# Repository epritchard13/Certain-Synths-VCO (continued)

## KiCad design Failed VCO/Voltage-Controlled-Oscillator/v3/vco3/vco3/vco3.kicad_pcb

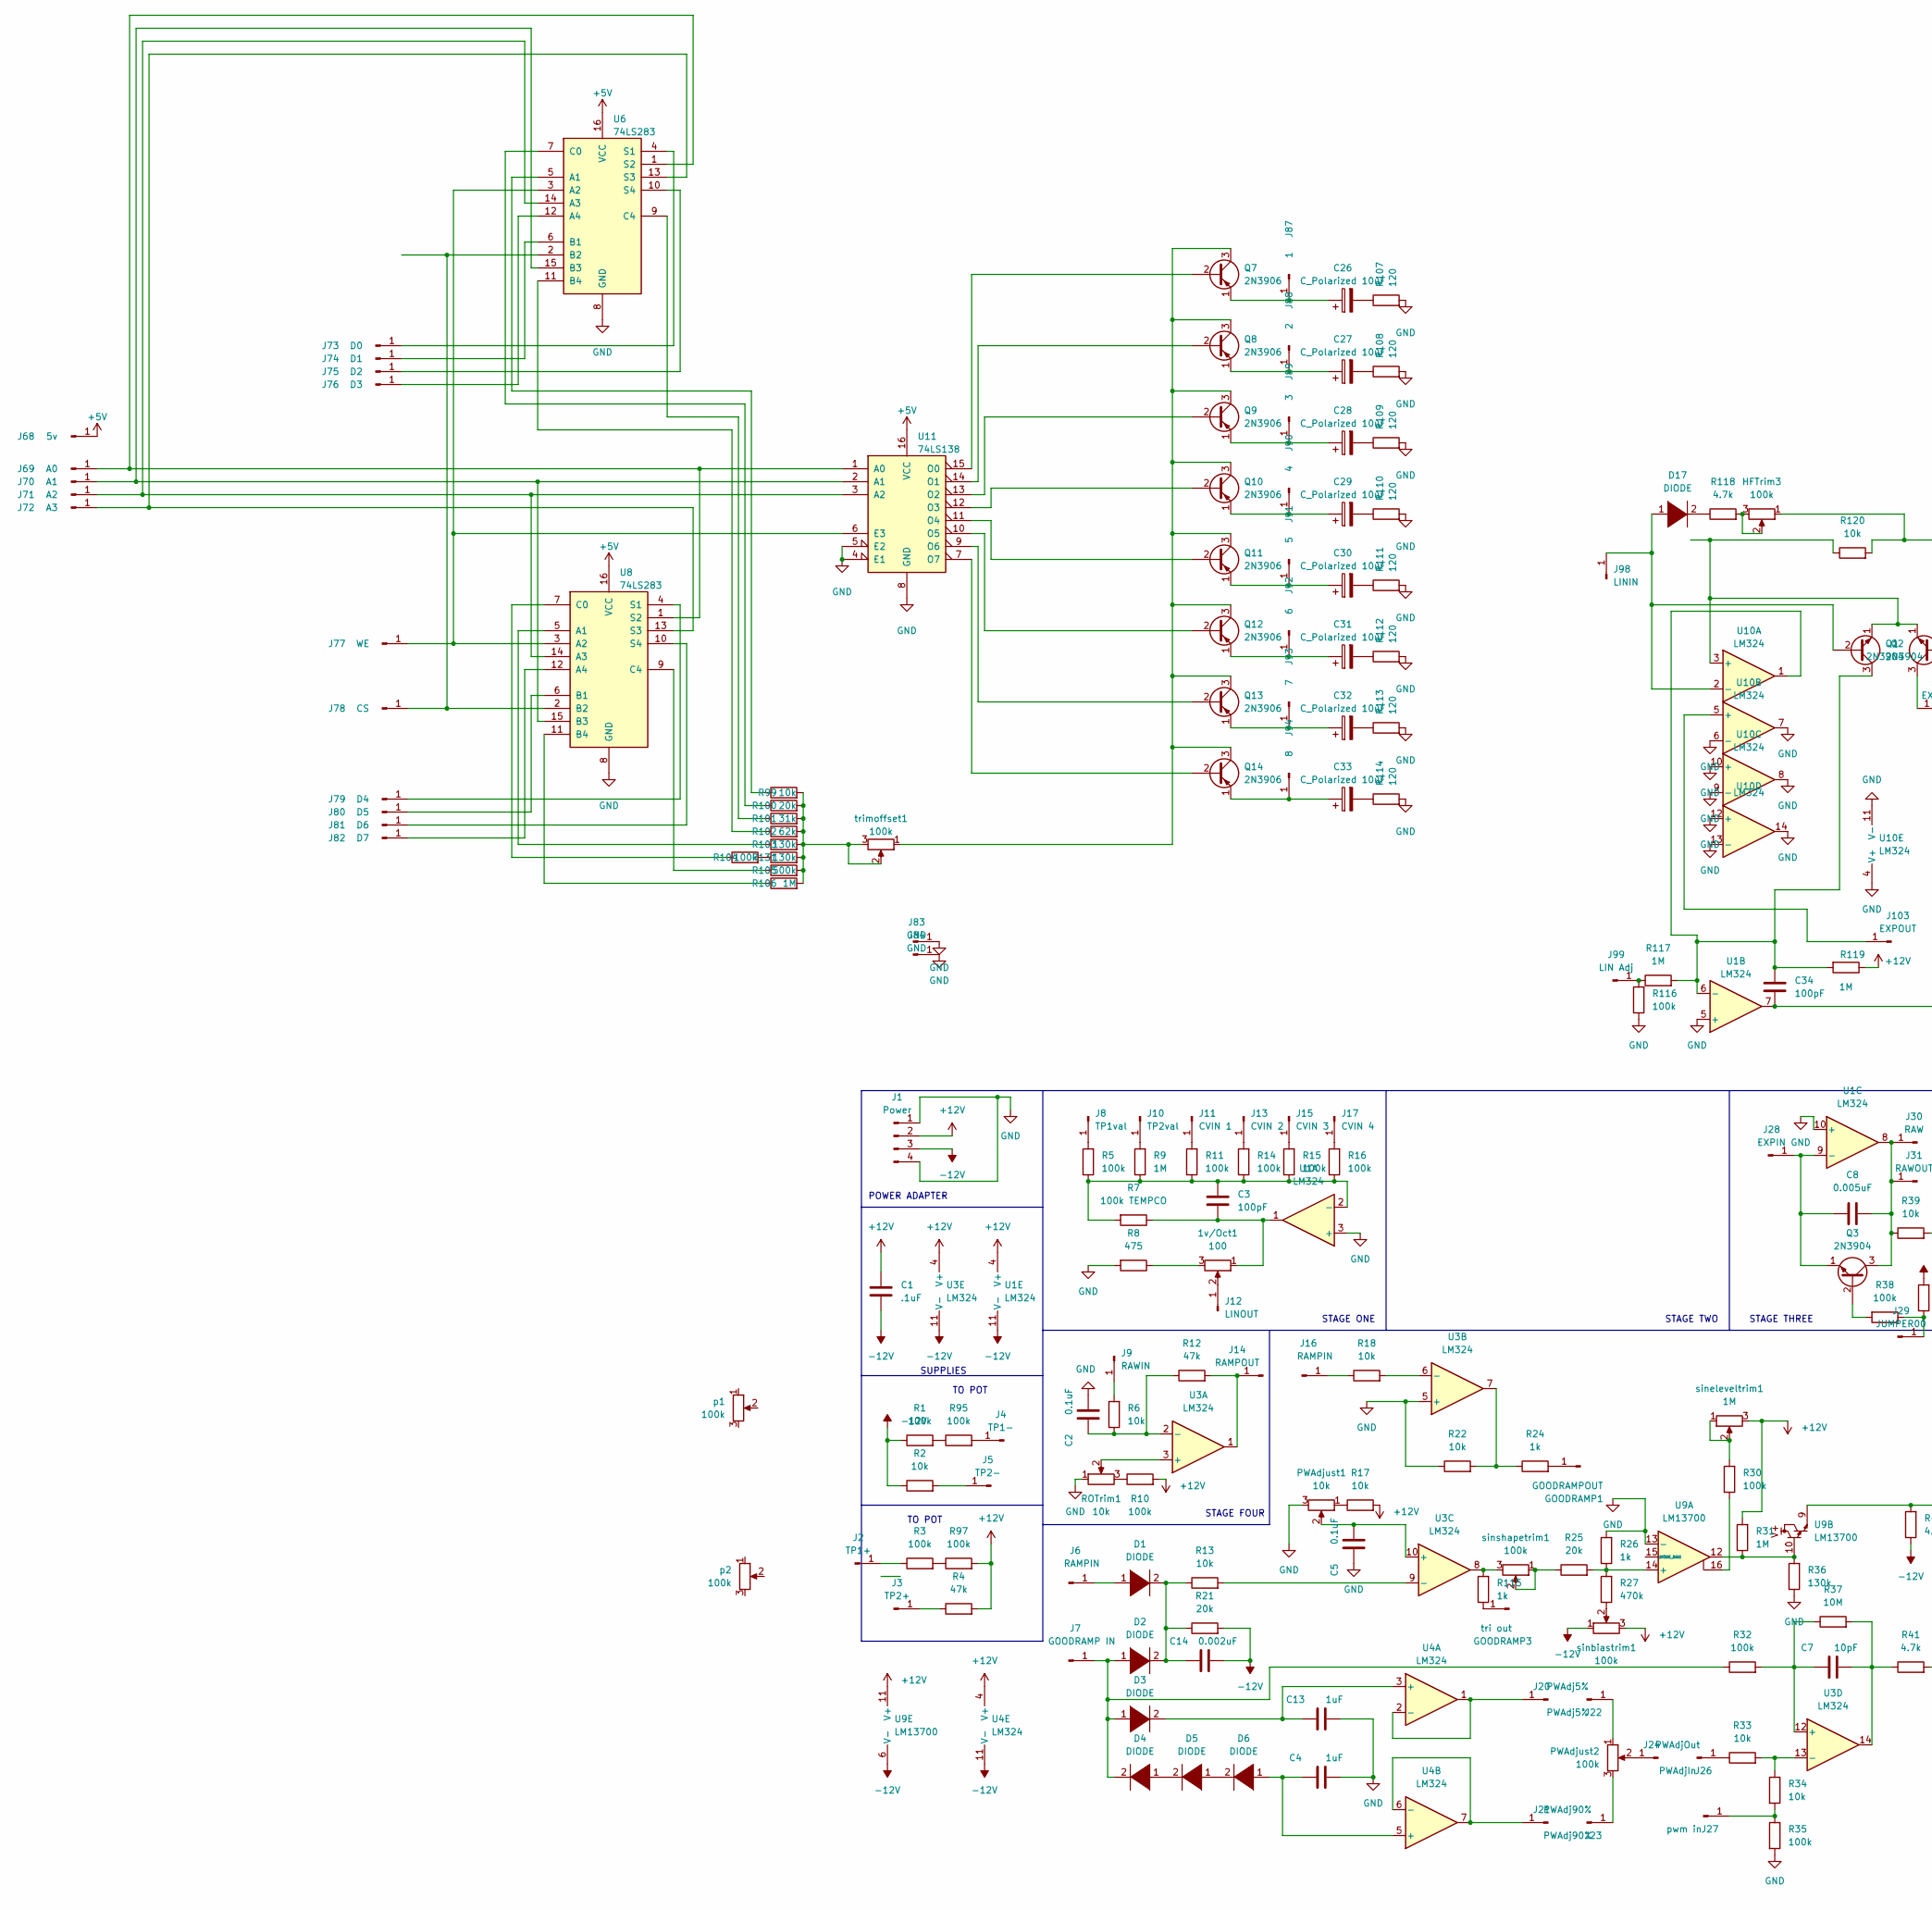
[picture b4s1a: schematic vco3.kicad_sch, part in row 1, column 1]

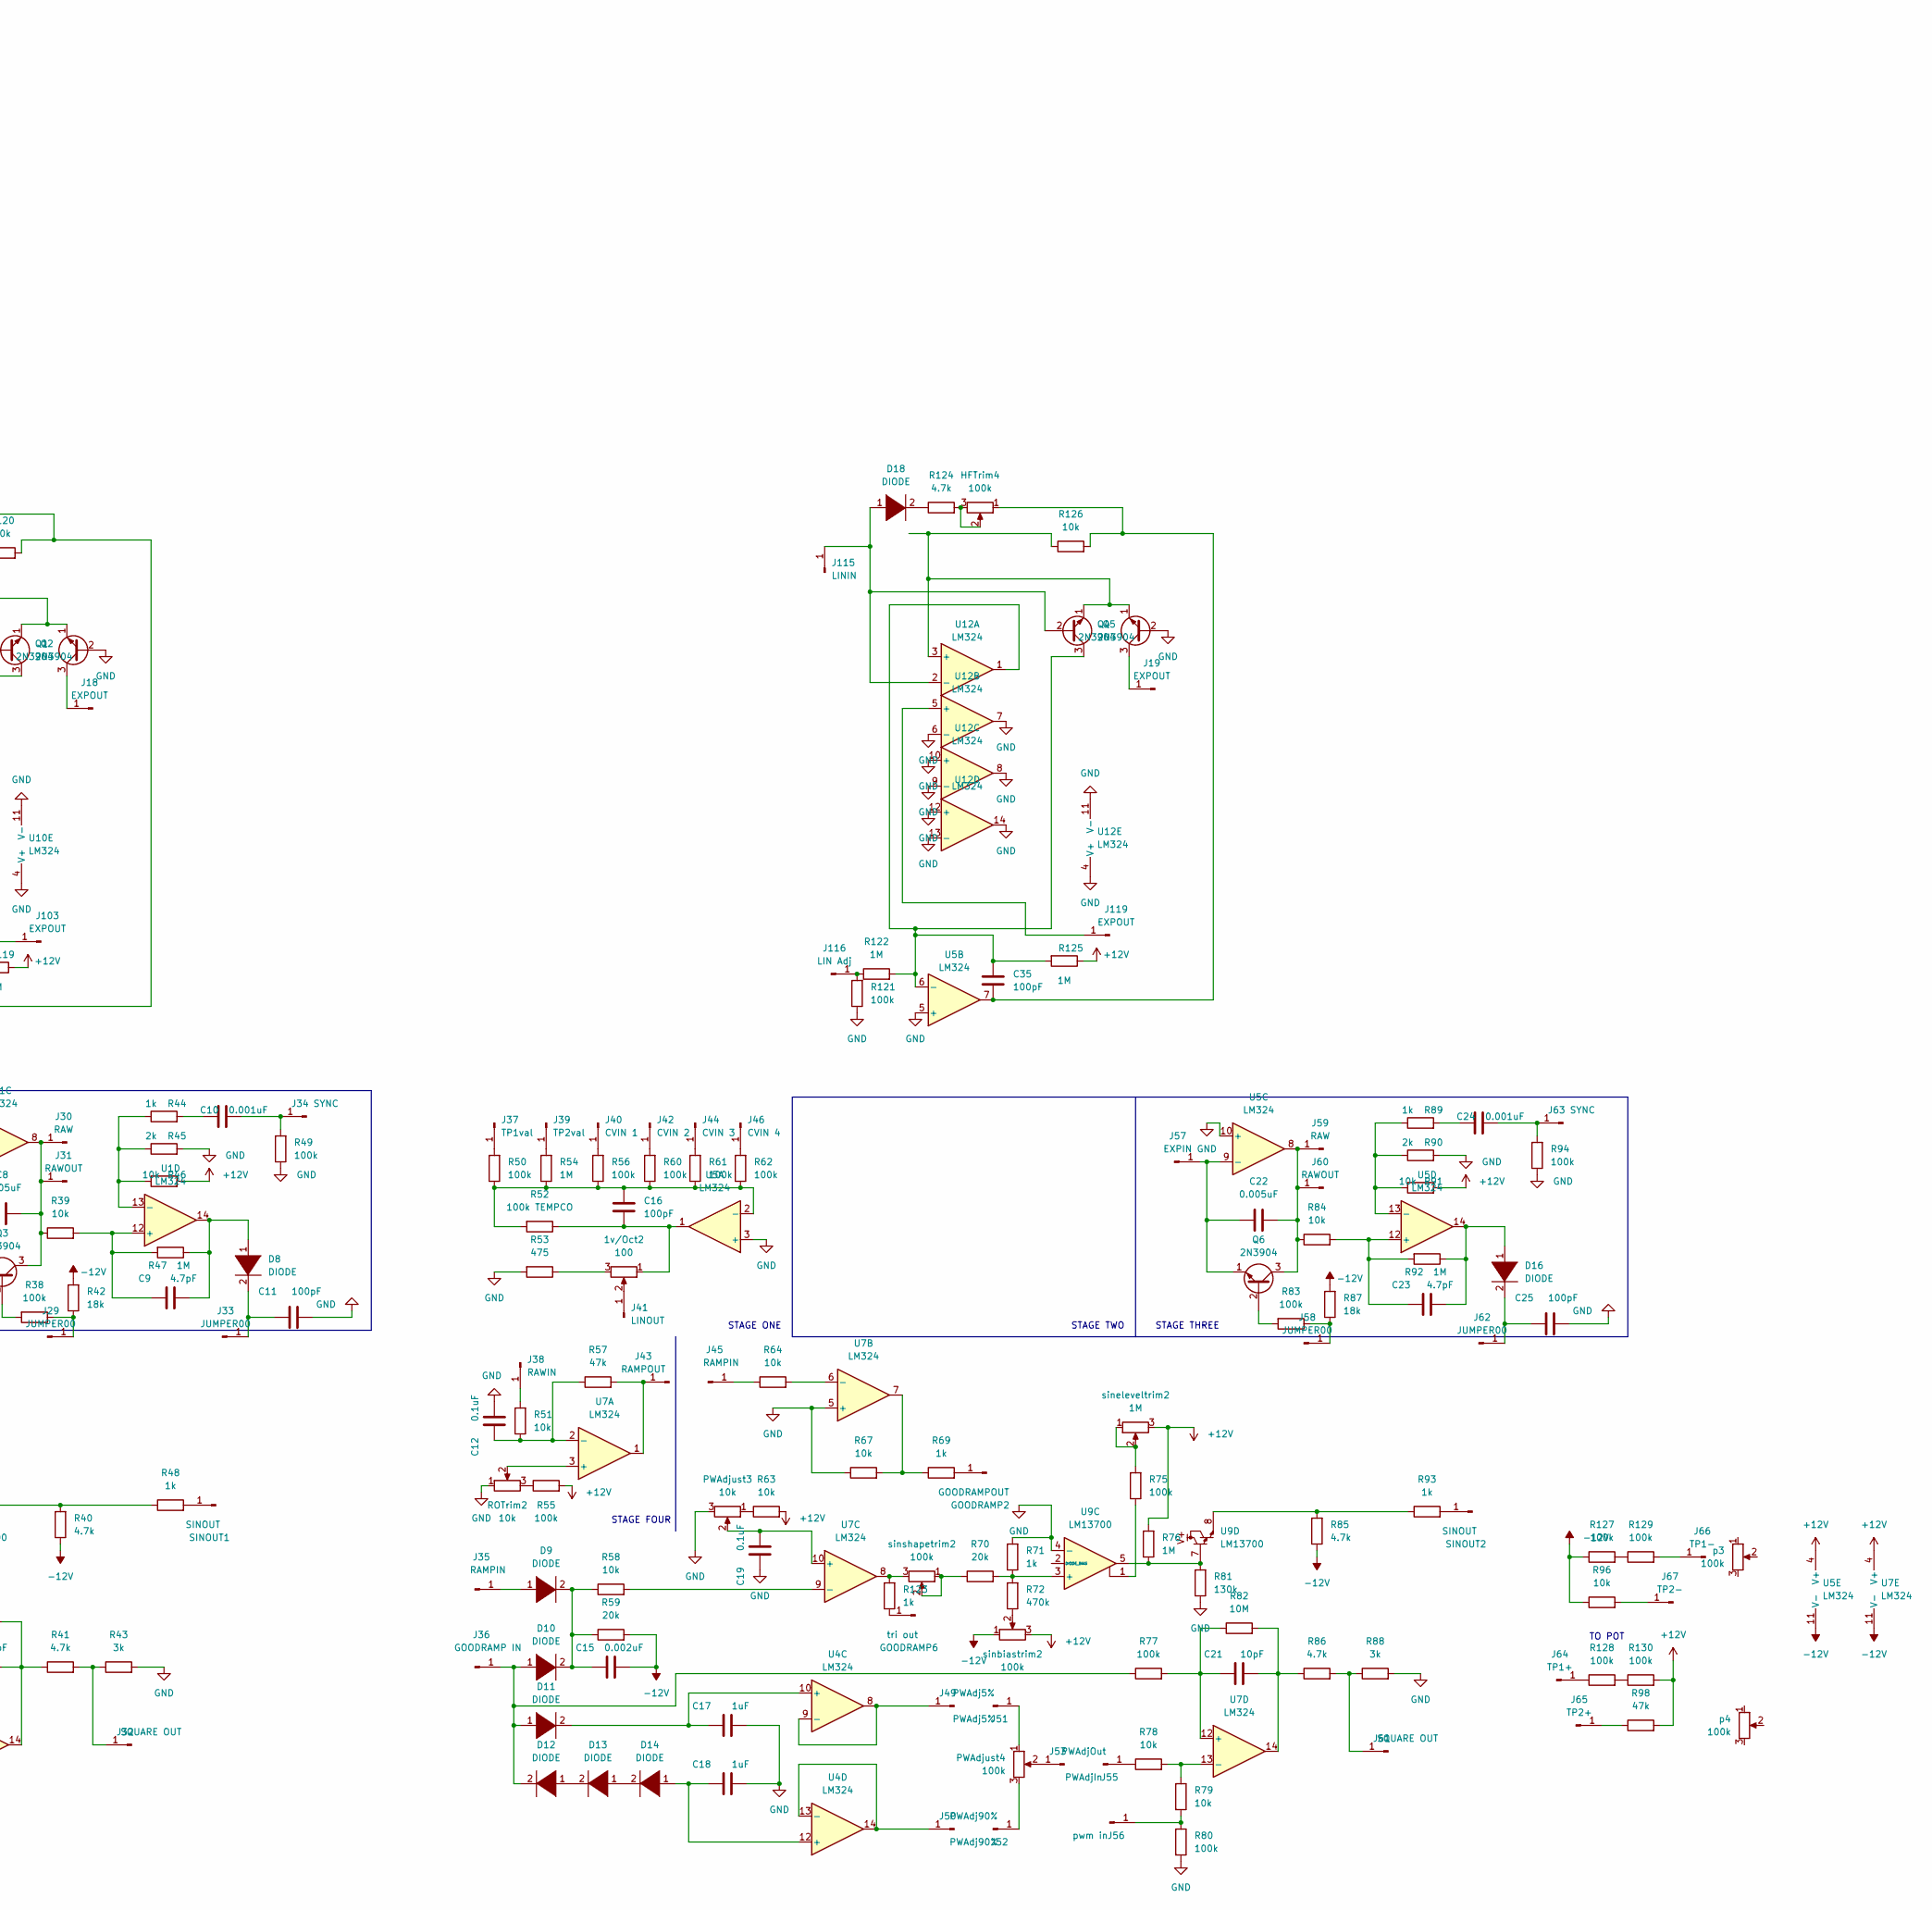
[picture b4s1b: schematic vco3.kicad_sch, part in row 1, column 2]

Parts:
1v/Oct1, 1v/Oct2: 100; Potentiometer_ACP_CA6-H2,5_Horizontal
C1: .1uF; C_Disc_D3.0mm_W2.0mm_P2.50mm
C2, C5, C12, C19: 0.1uF; C_Disc_D3.0mm_W2.0mm_P2.50mm
C3, C11, C16, C25, C34, C35: 100pF; C_Disc_D3.0mm_W2.0mm_P2.50mm
C4, C13, C17, C18: 1uF; C_Disc_D3.0mm_W2.0mm_P2.50mm
C7, C21: 10pF; C_1206_3216Metric_Pad1.33x1.80mm_HandSolder
C8, C22: 0.005uF; C_1206_3216Metric_Pad1.33x1.80mm_HandSolder
C9, C23: 4.7pF; C_1206_3216Metric_Pad1.33x1.80mm_HandSolder
C10, C24: 0.001uF; C_1206_3216Metric_Pad1.33x1.80mm_HandSolder
C14, C15: 0.002uF; C_1206_3216Metric_Pad1.33x1.80mm_HandSolder
C26, C27, C28, C29, C30, C31, C32, C33: C_Polarized 10uF; C_Disc_D3.0mm_W2.0mm_P2.50mm
D1, D2, D3, D4, D5, D6, D8, D9, D10, D11, D12, D13, D14, D16, D17, D18: DIODE; D_DO-35_SOD27_P2.54mm_Vertical_AnodeUp
GOODRAMP1, GOODRAMP2: GOODRAMPOUT; PinHeader_1x01_P2.54mm_Vertical
GOODRAMP3, GOODRAMP6: tri out; PinHeader_1x01_P2.54mm_Vertical
HFTrim3, HFTrim4: 100k; Potentiometer_ACP_CA6-H2,5_Horizontal
J1: Power; PinHeader_1x04_P2.54mm_Vertical
J2, J64: TP1+; PinHeader_1x01_P2.54mm_Vertical
J3, J65: TP2+; PinHeader_1x01_P2.54mm_Vertical
J4, J66: TP1-; PinHeader_1x01_P2.54mm_Vertical
J5, J67: TP2-; PinHeader_1x01_P2.54mm_Vertical
J6, J16, J35, J45: RAMPIN; PinHeader_1x01_P2.54mm_Vertical
J7, J36: GOODRAMP IN; PinHeader_1x01_P2.54mm_Vertical
J8, J37: TP1val; PinHeader_1x01_P2.54mm_Vertical
J9, J38: RAWIN; PinHeader_1x01_P2.54mm_Vertical
J10, J39: TP2val; PinHeader_1x01_P2.54mm_Vertical
J11, J40: CVIN 1; PinHeader_1x01_P2.54mm_Vertical
J12, J41: LINOUT; PinHeader_1x01_P2.54mm_Vertical
J13, J42: CVIN 2; PinHeader_1x01_P2.54mm_Vertical
J14, J43: RAMPOUT; PinHeader_1x01_P2.54mm_Vertical
J15, J44: CVIN 3; PinHeader_1x01_P2.54mm_Vertical
J17, J46: CVIN 4; PinHeader_1x01_P2.54mm_Vertical
J18, J19, J103, J119: EXPOUT; PinHeader_1x01_P2.54mm_Vertical
J20, J22, J49, J51: PWAdj5%; PinHeader_1x01_P2.54mm_Vertical
J21, J23, J50, J52: PWAdj90%; PinHeader_1x01_P2.54mm_Vertical
J24, J53: PWAdjOut; PinHeader_1x01_P2.54mm_Vertical
J26, J55: PWAdjIn; PinHeader_1x01_P2.54mm_Vertical
J27, J56: pwm in; PinHeader_1x01_P2.54mm_Vertical
J28, J57: EXPIN; PinHeader_1x01_P2.54mm_Vertical
J29, J33, J58, J62: JUMPER00; PinHeader_1x01_P2.54mm_Vertical
J30, J59: RAW; PinHeader_1x01_P2.54mm_Vertical
J31, J60: RAWOUT; PinHeader_1x01_P2.54mm_Vertical
J32, J61: SQUARE OUT; PinHeader_1x01_P2.54mm_Vertical
J34, J63: SYNC; PinHeader_1x01_P2.54mm_Vertical
J68: 5v; PinHeader_1x01_P2.54mm_Vertical
J69: A0; PinHeader_1x01_P2.54mm_Vertical
J70: A1; PinHeader_1x01_P2.54mm_Vertical
J71: A2; PinHeader_1x01_P2.54mm_Vertical
J72: A3; PinHeader_1x01_P2.54mm_Vertical
J73: D0; PinHeader_1x01_P2.54mm_Vertical
J74: D1; PinHeader_1x01_P2.54mm_Vertical
J75: D2; PinHeader_1x01_P2.54mm_Vertical
J76: D3; PinHeader_1x01_P2.54mm_Vertical
J77: WE; PinHeader_1x01_P2.54mm_Vertical
J78: CS; PinHeader_1x01_P2.54mm_Vertical
J79: D4; PinHeader_1x01_P2.54mm_Vertical
J80: D5; PinHeader_1x01_P2.54mm_Vertical
J81: D6; PinHeader_1x01_P2.54mm_Vertical
J82: D7; PinHeader_1x01_P2.54mm_Vertical
J83, J84: GND; PinHeader_1x01_P2.54mm_Vertical
J87: 1; PinHeader_1x01_P2.54mm_Vertical
J88: 2; PinHeader_1x01_P2.54mm_Vertical
J89: 3; PinHeader_1x01_P2.54mm_Vertical
J90: 4; PinHeader_1x01_P2.54mm_Vertical
J91: 5; PinHeader_1x01_P2.54mm_Vertical
J92: 6; PinHeader_1x01_P2.54mm_Vertical
J93: 7; PinHeader_1x01_P2.54mm_Vertical
J94: 8; PinHeader_1x01_P2.54mm_Vertical
J98, J115: LININ; PinHeader_1x01_P2.54mm_Vertical
J99, J116: LIN Adj; PinHeader_1x01_P2.54mm_Vertical
PWAdjust1, PWAdjust3: 10k; Potentiometer_ACP_CA6-H2,5_Horizontal
PWAdjust2, PWAdjust4: 100k; Potentiometer_ACP_CA6-H2,5_Horizontal
Q1, Q2, Q4, Q5: 2N3904; TO-92_Inline
Q3, Q6: 2N3904; TO-92
Q7, Q8, Q9, Q10, Q11, Q12, Q13, Q14: 2N3906; TO-92
R1, R3, R5, R10, R11, R14, R15, R16, R30, R32, R35, R38, R49, R50, R55, R56, R60, R61, R62, R75, R77, R80, R83, R94, R95, R97, R104, R116, R121, R127, R128, R129, R130: 100k; R_1206_3216Metric_Pad1.30x1.75mm_HandSolder
R2, R6, R13, R17, R18, R22, R33, R34, R39, R46, R51, R58, R63, R64, R67, R78, R79, R84, R91, R96, R99, R120, R126: 10k; R_1206_3216Metric_Pad1.30x1.75mm_HandSolder
R4, R12, R57, R98: 47k; R_Axial_DIN0204_L3.6mm_D1.6mm_P5.08mm_Horizontal
R7, R52: 100k TEMPCO; R_Axial_DIN0204_L3.6mm_D1.6mm_P5.08mm_Horizontal
R8, R53: 475; R_1206_3216Metric_Pad1.30x1.75mm_HandSolder
R9, R31, R47, R54, R76, R92, R106, R117, R119, R122, R125: 1M; R_Axial_DIN0204_L3.6mm_D1.6mm_P5.08mm_Horizontal
R21, R25, R59, R70, R100: 20k; R_1206_3216Metric_Pad1.30x1.75mm_HandSolder
R24, R26, R44, R48, R69, R71, R89, R93, R115, R123: 1k; R_1206_3216Metric_Pad1.30x1.75mm_HandSolder
R27, R72: 470k; R_1206_3216Metric_Pad1.30x1.75mm_HandSolder
R36, R81, R103, R131: 130k; R_1206_3216Metric_Pad1.30x1.75mm_HandSolder
R37, R82: 10M; R_Axial_DIN0204_L3.6mm_D1.6mm_P5.08mm_Horizontal
R40, R41, R85, R86, R118, R124: 4.7k; R_1206_3216Metric_Pad1.30x1.75mm_HandSolder
R42, R87: 18k; R_1206_3216Metric_Pad1.30x1.75mm_HandSolder
R43, R88: 3k; R_1206_3216Metric_Pad1.30x1.75mm_HandSolder
R45, R90: 2k; R_1206_3216Metric_Pad1.30x1.75mm_HandSolder
R101: 31k; R_1206_3216Metric_Pad1.30x1.75mm_HandSolder
R102: 62k; R_1206_3216Metric_Pad1.30x1.75mm_HandSolder
R105: 500k; R_1206_3216Metric_Pad1.30x1.75mm_HandSolder
R107, R108, R109, R110, R111, R112, R113, R114: 120; R_1206_3216Metric_Pad1.30x1.75mm_HandSolder
ROTrim1, ROTrim2: 10k; Potentiometer_ACP_CA6-H2,5_Horizontal
SINOUT1, SINOUT2: SINOUT; PinHeader_1x01_P2.54mm_Vertical
U1, U3, U4, U5, U7, U10, U12: LM324; DIP-14_W7.62mm
U6, U8: 74LS283; DIP-16_W7.62mm
U9: LM13700; DIP-16_W7.62mm
U11: 74LS138; DIP-16_W7.62mm
p1, p2, p3, p4: 100k; Potentiometer_ACP_CA6-H2,5_Horizontal
sinbiastrim1, sinbiastrim2: 100k; Potentiometer_ACP_CA6-H2,5_Horizontal
sineleveltrim1, sineleveltrim2: 1M; Potentiometer_ACP_CA6-H2,5_Horizontal
sinshapetrim1, sinshapetrim2: 100k; Potentiometer_ACP_CA6-H2,5_Horizontal
trimoffset1: 100k; Potentiometer_ACP_CA6-H2,5_Horizontal

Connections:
+5V: J68.1, U6.16 (VCC), U8.16 (VCC), U11.16 (VCC)
+12V: C1.1, J1.2, R4.2, R10.2, R17.2, R31.2, R46.2, R55.2, R63.2, R76.2, R91.2, R97.2, R98.2, R119.1, R125.1, R130.2, U1.4 (V+), U3.4 (V+), U4.4 (V+), U5.4 (V+), U7.4 (V+), U9.11 (V+), sinbiastrim1.3, sinbiastrim2.3, sineleveltrim1.3, sineleveltrim2.3
-12V: C1.2, C14.2, C15.2, J1.3, R1.1, R2.1, R21.2, R40.1, R42.2, R59.2, R85.1, R87.2, R96.1, R127.1, U1.11 (V-), U3.11 (V-), U4.11 (V-), U5.11 (V-), U7.11 (V-), U9.6 (V-), sinbiastrim1.1, sinbiastrim2.1
GND: C2.2, C4.2, C5.1, C11.2, C12.2, C13.2, C17.2, C18.2, C19.1, C25.2, J1.1, J1.4, J83.1, J84.1, PWAdjust1.3, PWAdjust3.3, Q2.2 (B), Q5.2 (B), R8.2, R22.1, R26.2, R35.2, R36.1, R43.2, R45.2, R49.1, R53.2, R67.1, R71.2, R80.2, R81.1, R88.2, R90.2, R94.1, R107.2, R108.2, R109.2, R110.2, R111.2, R112.2, R113.2, R114.2, R116.1, R121.1, ROTrim1.1, ROTrim2.1, U1.3 (+), U1.5 (+), U1.10 (+), U3.5 (+), U5.3 (+), U5.5 (+), U5.10 (+), U6.8 (GND), U7.5 (+), U8.8 (GND), U9.4 (-), U9.13 (-), U10.4 (V+), U10.6 (-), U10.7, U10.8, U10.9 (-), U10.10 (+), U10.11 (V-), U10.12 (+), U10.13 (-), U10.14, U11.4 (E1), U11.5 (E2), U11.8 (GND), U12.4 (V+), U12.6 (-), U12.7, U12.8, U12.9 (-), U12.10 (+), U12.11 (V-), U12.12 (+), U12.13 (-), U12.14
unnamed: 1v/Oct1.1, C3.2, R7.1, U1.1
unnamed: 1v/Oct1.2, J12.1
unnamed: 1v/Oct1.3, R8.1
unnamed: 1v/Oct2.1, C16.2, R52.1, U5.1
unnamed: 1v/Oct2.2, J41.1
unnamed: 1v/Oct2.3, R53.1
unnamed: C2.1, R6.1, R12.1, U3.2 (-)
unnamed: C3.1, R5.1, R7.2, R9.1, R11.1, R14.1, R15.1, R16.1, U1.2 (-)
unnamed: C4.1, D6.1 (K), U4.5 (+)
unnamed: C5.2, PWAdjust1.2, U3.10 (+)
unnamed: C7.1, R32.2, R37.1, U3.12 (+)
unnamed: C7.2, R37.2, R41.1, U3.14
unnamed: C8.1, J28.1, Q3.1 (E), U1.9 (-)
unnamed: C8.2, J30.1, J31.1, Q3.3 (C), R39.1, U1.8
unnamed: C9.1, R39.2, R47.2, U1.12 (+)
unnamed: C9.2, D8.1 (K), R47.1, U1.14
unnamed: C10.1, R44.2
unnamed: C10.2, J34.1, R49.2
unnamed: C11.1, D8.2 (A), J33.1
unnamed: C12.1, R51.1, R57.1, U7.2 (-)
unnamed: C13.1, D3.2 (A), U4.3 (+)
unnamed: C14.1, D1.2 (A), D2.2 (A), R13.1, R21.1
unnamed: C15.1, D9.2 (A), D10.2 (A), R58.1, R59.1
unnamed: C16.1, R50.1, R52.2, R54.1, R56.1, R60.1, R61.1, R62.1, U5.2 (-)
unnamed: C17.1, D11.2 (A), U4.10 (+)
unnamed: C18.1, D14.1 (K), U4.12 (+)
unnamed: C19.2, PWAdjust3.2, U7.10 (+)
unnamed: C21.1, R77.2, R82.1, U7.12 (+)
unnamed: C21.2, R82.2, R86.1, U7.14
unnamed: C22.1, J57.1, Q6.1 (E), U5.9 (-)
unnamed: C22.2, J59.1, J60.1, Q6.3 (C), R84.1, U5.8
unnamed: C23.1, R84.2, R92.2, U5.12 (+)
unnamed: C23.2, D16.1 (K), R92.1, U5.14
unnamed: C24.1, R89.2
unnamed: C24.2, J63.1, R94.2
unnamed: C25.1, D16.2 (A), J62.1
unnamed: C26.1, J87.1, Q7.1 (E)
unnamed: C26.2, R107.1
unnamed: C27.1, J88.1, Q8.1 (E)
unnamed: C27.2, R108.1
unnamed: C28.1, J89.1, Q9.1 (E)
unnamed: C28.2, R109.1
unnamed: C29.1, J90.1, Q10.1 (E)
unnamed: C29.2, R110.1
unnamed: C30.1, J91.1, Q11.1 (E)
unnamed: C30.2, R111.1
unnamed: C31.1, J92.1, Q12.1 (E)
unnamed: C31.2, R112.1
unnamed: C32.1, J93.1, Q13.1 (E)
unnamed: C32.2, R113.1
unnamed: C33.1, J94.1, Q14.1 (E)
unnamed: C33.2, R114.1
unnamed: C34.1, Q1.3 (C), R117.2, R119.2, U1.6 (-), U10.1
unnamed: C34.2, HFTrim3.1, R120.2, U1.7
unnamed: C35.1, Q4.3 (C), R122.2, R125.2, U5.6 (-), U12.1
unnamed: C35.2, HFTrim4.1, R126.2, U5.7
unnamed: D1.1 (K), J6.1
unnamed: D2.1 (K), D3.1 (K), D4.2 (A), J7.1, R32.1
unnamed: D4.1 (K), D5.2 (A)
unnamed: D5.1 (K), D6.2 (A)
unnamed: D9.1 (K), J35.1
unnamed: D10.1 (K), D11.1 (K), D12.2 (A), J36.1, R77.1
unnamed: D12.1 (K), D13.2 (A)
unnamed: D13.1 (K), D14.2 (A)
unnamed: D17.1 (K), J98.1, Q1.2 (B), U10.2 (-)
unnamed: D17.2 (A), R118.1
unnamed: D18.1 (K), J115.1, Q4.2 (B), U12.2 (-)
unnamed: D18.2 (A), R124.1
unnamed: GOODRAMP1.1, R24.2
unnamed: GOODRAMP2.1, R69.2
unnamed: GOODRAMP3.1, R115.1
unnamed: GOODRAMP6.1, R123.1
unnamed: HFTrim3.2, HFTrim3.3, R118.2
unnamed: HFTrim4.2, HFTrim4.3, R124.2
unnamed: J2.1, R3.1
unnamed: J3.1, R4.1
unnamed: J4.1, R95.2
unnamed: J5.1, R2.2
unnamed: J8.1, R5.2
unnamed: J9.1, R6.2
unnamed: J10.1, R9.2
unnamed: J11.1, R11.2
unnamed: J13.1, R14.2
unnamed: J14.1, R12.2, U3.1
unnamed: J15.1, R15.2
unnamed: J16.1, R18.1
unnamed: J17.1, R16.2
unnamed: J18.1, Q2.3 (C)
unnamed: J19.1, Q5.3 (C)
unnamed: J20.1, U4.1, U4.2 (-)
unnamed: J21.1, U4.6 (-), U4.7
unnamed: J22.1, PWAdjust2.1
unnamed: J23.1, PWAdjust2.3
unnamed: J24.1, PWAdjust2.2
unnamed: J26.1, R33.1
unnamed: J27.1, R34.2, R35.1
unnamed: J29.1, R38.1, R42.1
unnamed: J32.1, R41.2, R43.1
unnamed: J37.1, R50.2
unnamed: J38.1, R51.2
unnamed: J39.1, R54.2
unnamed: J40.1, R56.2
unnamed: J42.1, R60.2
unnamed: J43.1, R57.2, U7.1
unnamed: J44.1, R61.2
unnamed: J45.1, R64.1
unnamed: J46.1, R62.2
unnamed: J49.1, U4.8, U4.9 (-)
unnamed: J50.1, U4.13 (-), U4.14
unnamed: J51.1, PWAdjust4.1
unnamed: J52.1, PWAdjust4.3
unnamed: J53.1, PWAdjust4.2
unnamed: J55.1, R78.1
unnamed: J56.1, R79.2, R80.1
unnamed: J58.1, R83.1, R87.1
unnamed: J61.1, R86.2, R88.1
unnamed: J64.1, R128.1
unnamed: J65.1, R98.1
unnamed: J66.1, R129.2
unnamed: J67.1, R96.2
unnamed: J69.1, U6.1 (S2), U8.1 (S2), U11.1 (A0)
unnamed: J70.1, U6.15 (B3), U8.15 (B3), U11.2 (A1)
unnamed: J71.1, U6.14 (A3), U8.14 (A3), U11.3 (A2)
unnamed: J72.1, U6.13 (S3), U8.13 (S3)
unnamed: J73.1, U6.4 (S1)
unnamed: J74.1, U6.6 (B1)
unnamed: J75.1, U6.10 (S4)
unnamed: J76.1, U6.12 (A4)
unnamed: J77.1, U6.3 (A2), U8.3 (A2), U11.6 (E3)
unnamed: J78.1, U6.2 (B2), U8.2 (B2)
unnamed: J79.1, U8.4 (S1)
unnamed: J80.1, U8.6 (B1)
unnamed: J81.1, U8.10 (S4)
unnamed: J82.1, U8.12 (A4)
unnamed: J99.1, R116.2, R117.1
unnamed: J103.1, U10.5 (+)
unnamed: J116.1, R121.2, R122.1
unnamed: J119.1, U12.5 (+)
unnamed: PWAdjust1.1, R17.1
unnamed: PWAdjust3.1, R63.1
unnamed: Q1.1 (E), Q2.1 (E), R120.1, U10.3 (+)
unnamed: Q3.2 (B), R38.2
unnamed: Q4.1 (E), Q5.1 (E), R126.1, U12.3 (+)
unnamed: Q6.2 (B), R83.2
unnamed: Q7.2 (B), U11.15 (O0)
unnamed: Q8.2 (B), U11.14 (O1)
unnamed: Q9.2 (B), U11.13 (O2)
unnamed: Q10.2 (B), U11.12 (O3)
unnamed: Q7.3 (C), Q8.3 (C), Q9.3 (C), Q10.3 (C), Q11.3 (C), Q12.3 (C), Q13.3 (C), Q14.3 (C), trimoffset1.1
unnamed: Q11.2 (B), U11.11 (O4)
unnamed: Q12.2 (B), U11.10 (O5)
unnamed: Q13.2 (B), U11.9 (O6)
unnamed: Q14.2 (B), U11.7 (O7)
unnamed: R1.2, R95.1
unnamed: R3.2, R97.1
unnamed: R10.1, ROTrim1.3
unnamed: R13.2, U3.9 (-)
unnamed: R18.2, U3.6 (-)
unnamed: R22.2, R24.1, U3.7
unnamed: R25.1, sinshapetrim1.1, sinshapetrim1.2
unnamed: R25.2, R26.1, R27.2, U9.14 (+)
unnamed: R27.1, sinbiastrim1.2
unnamed: R30.1, U9.16
unnamed: R30.2, sineleveltrim1.1, sineleveltrim1.2
unnamed: R31.1, R36.2, U9.10, U9.12
unnamed: R33.2, R34.1, U3.13 (-)
unnamed: R40.2, R48.1, U9.9
unnamed: R44.1, R45.1, R46.1, U1.13 (-)
unnamed: R48.2, SINOUT1.1
unnamed: R55.1, ROTrim2.3
unnamed: R58.2, U7.9 (-)
unnamed: R64.2, U7.6 (-)
unnamed: R67.2, R69.1, U7.7
unnamed: R70.1, sinshapetrim2.1, sinshapetrim2.2
unnamed: R70.2, R71.1, R72.2, U9.3 (+)
unnamed: R72.1, sinbiastrim2.2
unnamed: R75.1, U9.1
unnamed: R75.2, sineleveltrim2.1, sineleveltrim2.2
unnamed: R76.1, R81.2, U9.5, U9.7
unnamed: R78.2, R79.1, U7.13 (-)
unnamed: R85.2, R93.1, U9.8
unnamed: R89.1, R90.1, R91.1, U5.13 (-)
unnamed: R93.2, SINOUT2.1
unnamed: R99.1, U6.5 (A1)
unnamed: R100.1, U6.7 (C0)
unnamed: R99.2, R100.2, R101.2, R102.2, R103.2, R105.2, R106.2, R131.2, trimoffset1.2, trimoffset1.3
unnamed: R101.1, U6.9 (C4)
unnamed: R102.1, U6.11 (B4)
unnamed: R103.1, U8.5 (A1)
unnamed: R104.1, U8.7 (C0)
unnamed: R104.2, R131.1
unnamed: R105.1, U8.9 (C4)
unnamed: R106.1, U8.11 (B4)
unnamed: R115.2, U3.8, sinshapetrim1.3
unnamed: R123.2, U7.8, sinshapetrim2.3
unnamed: R127.2, R129.1
unnamed: R128.2, R130.1
unnamed: ROTrim1.2, U3.3 (+)
unnamed: ROTrim2.2, U7.3 (+)

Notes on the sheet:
POWER ADAPTER
STAGE FOUR
TO POT
STAGE TWO
STAGE ONE
STAGE THREE
SUPPLIES

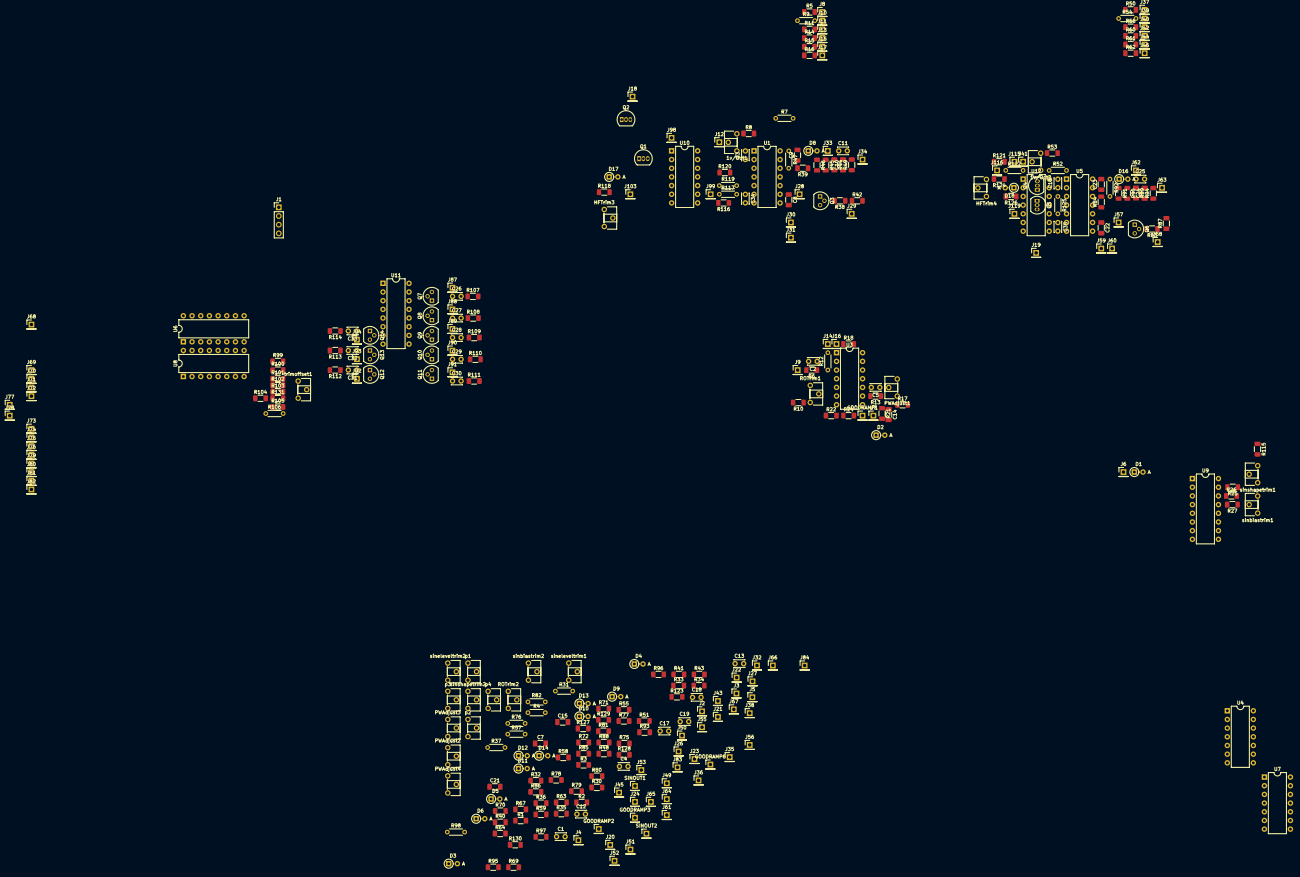
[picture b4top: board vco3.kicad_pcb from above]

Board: 2 copper layers, 316 parts (0 on the bottom side), 203 nets.

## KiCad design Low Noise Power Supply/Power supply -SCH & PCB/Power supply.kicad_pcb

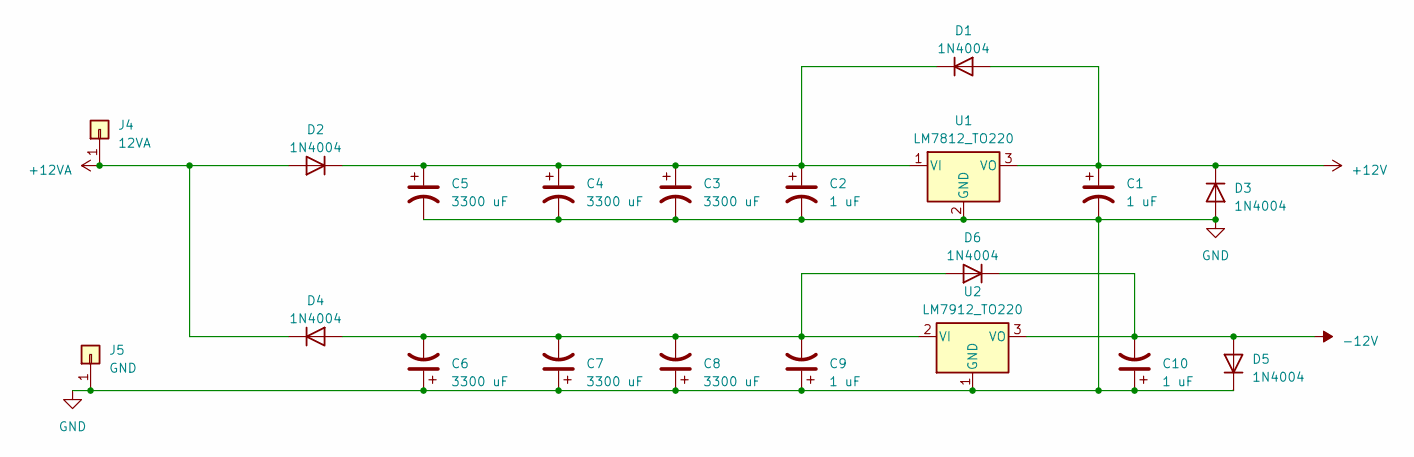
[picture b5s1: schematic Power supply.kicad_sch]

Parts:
C1, C2, C9, C10: 1 uF; CP_Radial_Tantal_D4.5mm_P5.00mm
C3, C4, C5, C6, C7, C8: 3300 uF; CP_Radial_D16.0mm_P7.50mm
D1, D2, D3, D4, D5, D6: 1N4004; D_DO-41_SOD81_P10.16mm_Horizontal
J4: 12VA; PinSocket_1x01_P2.54mm_Vertical
J5: GND; PinSocket_1x01_P2.54mm_Vertical
U1: LM7812_TO220; TO-220-3_Vertical
U2: LM7912_TO220; TO-220-3_Vertical

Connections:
+12V: C1.1, D1.2 (A), D3.1 (K), U1.3 (VO)
+12VA: D2.2 (A), D4.1 (K), J4.1
-12V: C10.2, D5.2 (A), D6.1 (K), U2.3 (VO)
GND: C1.2, C2.2, C3.2, C4.2, C5.2, C6.1, C7.1, C8.1, C9.1, C10.1, D3.2 (A), D5.1 (K), J5.1, U1.2 (GND), U2.1 (GND)
unnamed: C2.1, C3.1, C4.1, C5.1, D1.1 (K), D2.1 (K), U1.1 (VI)
unnamed: C6.2, C7.2, C8.2, C9.2, D4.2 (A), D6.2 (A), U2.2 (VI)

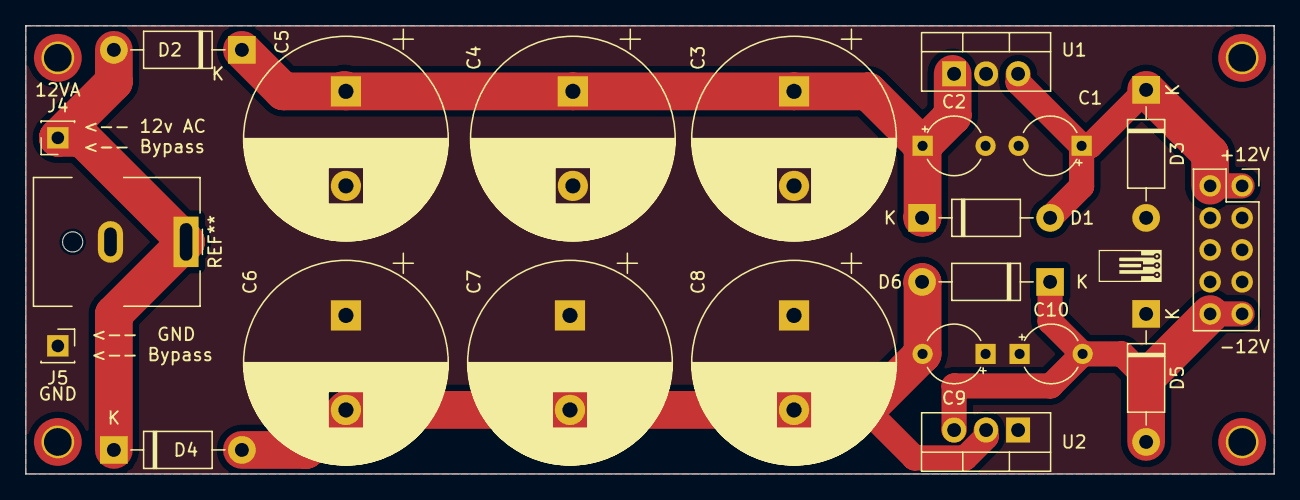
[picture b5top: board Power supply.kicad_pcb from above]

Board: 2 copper layers, 99.1 x 35.6 mm, 20 parts (0 on the bottom side), 6 nets.

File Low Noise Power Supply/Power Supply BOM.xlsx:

Part Number | Description | Distrubuter | Cost per unit | Amount | Total Cost | Link
493-1307-ND | 3300 uF Electrolydic Cap | Digikey | 1.1399999999999999 | 6 | 6.84 | https://www.digikey.com/en/products/detail/nichicon/UVZ1E332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
478-TAP105K035CRSCT-ND | 1 uF Tant Cap | Digikey | 0.46 | 4 | 1.84 | https://www.digikey.com/en/products/detail/kyocera-avx/TAP10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
1N4004DICT-ND | 1N4004 Diode | Digikey | 0.2 | 5 | 1 | https://www.digikey.com/en/products/detail/diodes-incorporat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
LM340T-12/NOPB-ND | 12 V IC Regulator (LM7812) | Digikey | 1.91 | 1 | 1.91 | https://www.digikey.com/en/products/detail/texas-instruments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
LM7912CT/NOPB-ND | -12 V IC Regulator (LM7912) | Digikey | 1.59 | 1 | 1.59 | https://www.digikey.com/en/products/detail/texas-instruments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
237-1879-ND | AC/AC WALL MNT ADAPTER 12V 1.5A | Digikey | 16.760000000000002 | 1 | 16.760000000000002 | https://www.digikey.com/en/products/detail/triad-magnetics/W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
CP-037A-ND | Power Barrel Connector | Digikey | 0.69 | 1 | 0.69 | https://www.digikey.com/en/products/detail/cui-devices/PJ-03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
 |  |  |  |  | 0
 |  |  |  |  | 0
 |  |  |  |  | 0
 |  |  |  |  | 0
 |  |  |  |  | 0
 |  |  |  |  | 0
 |  |  |  |  | 0
 |  |  |  |  | 0
 |  |  |  | Total | 30.630000000000003

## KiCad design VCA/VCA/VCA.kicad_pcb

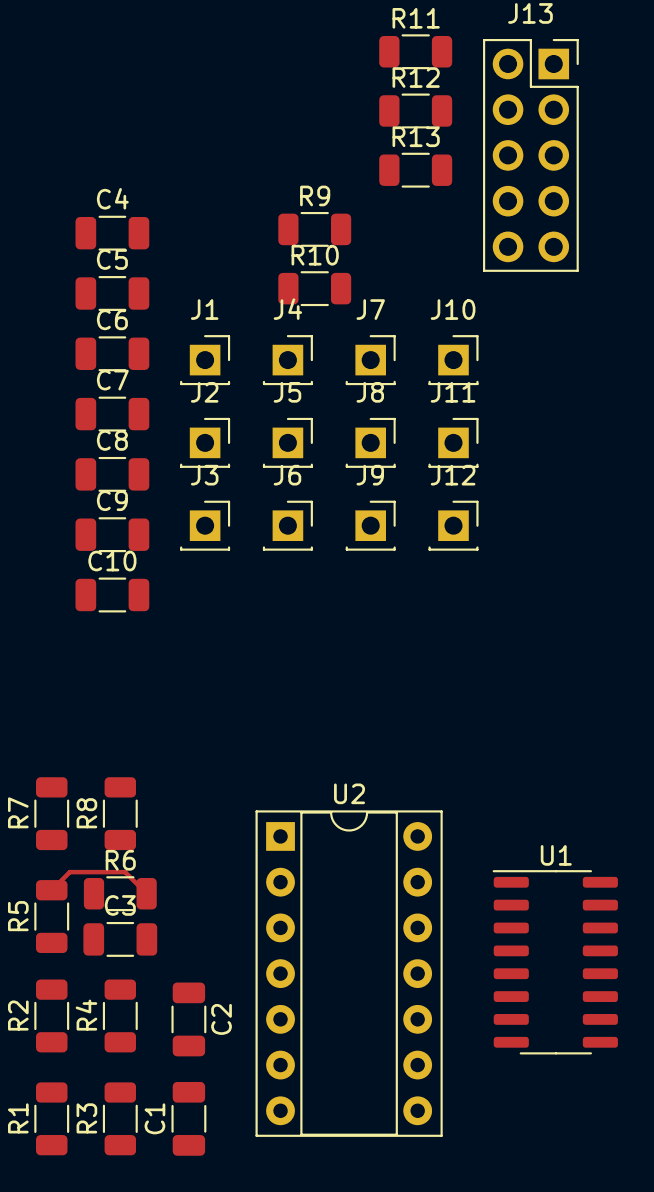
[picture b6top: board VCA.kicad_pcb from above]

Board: 2 copper layers, 38 parts (0 on the bottom side), 20 nets.

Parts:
C1, C2, C3, C4: 560pF; C_1206_3216Metric
C5, C6: 1uF; C_1206_3216Metric
C7, C8, C9, C10: 100pF; C_1206_3216Metric
J1: VCO1; PinSocket_1x01_P2.54mm_Vertical
J2: VCO2; PinSocket_1x01_P2.54mm_Vertical
J3: VCO3; PinSocket_1x01_P2.54mm_Vertical
J4: VCO4; PinSocket_1x01_P2.54mm_Vertical
J5: Q1; PinSocket_1x01_P2.54mm_Vertical
J6, J8: Q2; PinSocket_1x01_P2.54mm_Vertical
J7: Q3; PinSocket_1x01_P2.54mm_Vertical
J9: ADSR4; PinSocket_1x01_P2.54mm_Vertical
J10: ADSR3; PinSocket_1x01_P2.54mm_Vertical
J11: ADSR2; PinSocket_1x01_P2.54mm_Vertical
J12: ADSR1; PinSocket_1x01_P2.54mm_Vertical
J13: Conn_02x05_Odd_Even; PinSocket_2x05_P2.54mm_Vertical
R1, R3, R5, R7, R10, R11, R12, R13: 30k; R_1206_3216Metric
R2, R4, R6, R8: 500; R_1206_3216Metric
R9: 7.5k; R_1206_3216Metric
U1: SSI2164; SOIC-16_3.9x9.9mm_P1.27mm
U2: LM324; DIP-14_W7.62mm_Socket

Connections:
+12V: C5.2, J13.1, J13.2, R9.2, U1.16 (V+)
-12V: C6.1, J13.9, J13.10, U1.9 (V-)
GND: C1.2, C2.2, C3.2, C4.2, C5.1, C6.2, J13.3, J13.4, J13.5, J13.6, J13.7, J13.8, U1.8 (GND), U2.3 (+), U2.5 (+), U2.10 (+), U2.12 (+)
unnamed: C1.1, R2.1
unnamed: C2.1, R4.1
unnamed: C3.1, R6.1
unnamed: C4.1, R8.1
unnamed: R1.2, R2.2, U1.2 (I_IN1)
unnamed: R3.2, R4.2, U1.7 (I_IN2)
unnamed: R5.2, R6.2, U1.10 (I_IN3)
unnamed: R7.2, R8.2, U1.15 (I_IN4)
unnamed: C7.2, R10.1, U1.4 (I_OUT1), U2.2 (-)
unnamed: C8.2, R11.1, U1.5 (I_OUT2), U2.6 (-)
unnamed: C9.2, R12.1, U1.12 (I_OUT3), U2.9 (-)
unnamed: C10.2, R13.1, U1.13 (I_OUT4), U2.13 (-)
unnamed: R9.1, U1.1 (MODE)
Out1: C7.1, R10.2, U2.1
Out2: C8.1, R11.2, U2.7
Out3: C9.1, R12.2, U2.8
Out4: C10.1, R13.2, U2.14
